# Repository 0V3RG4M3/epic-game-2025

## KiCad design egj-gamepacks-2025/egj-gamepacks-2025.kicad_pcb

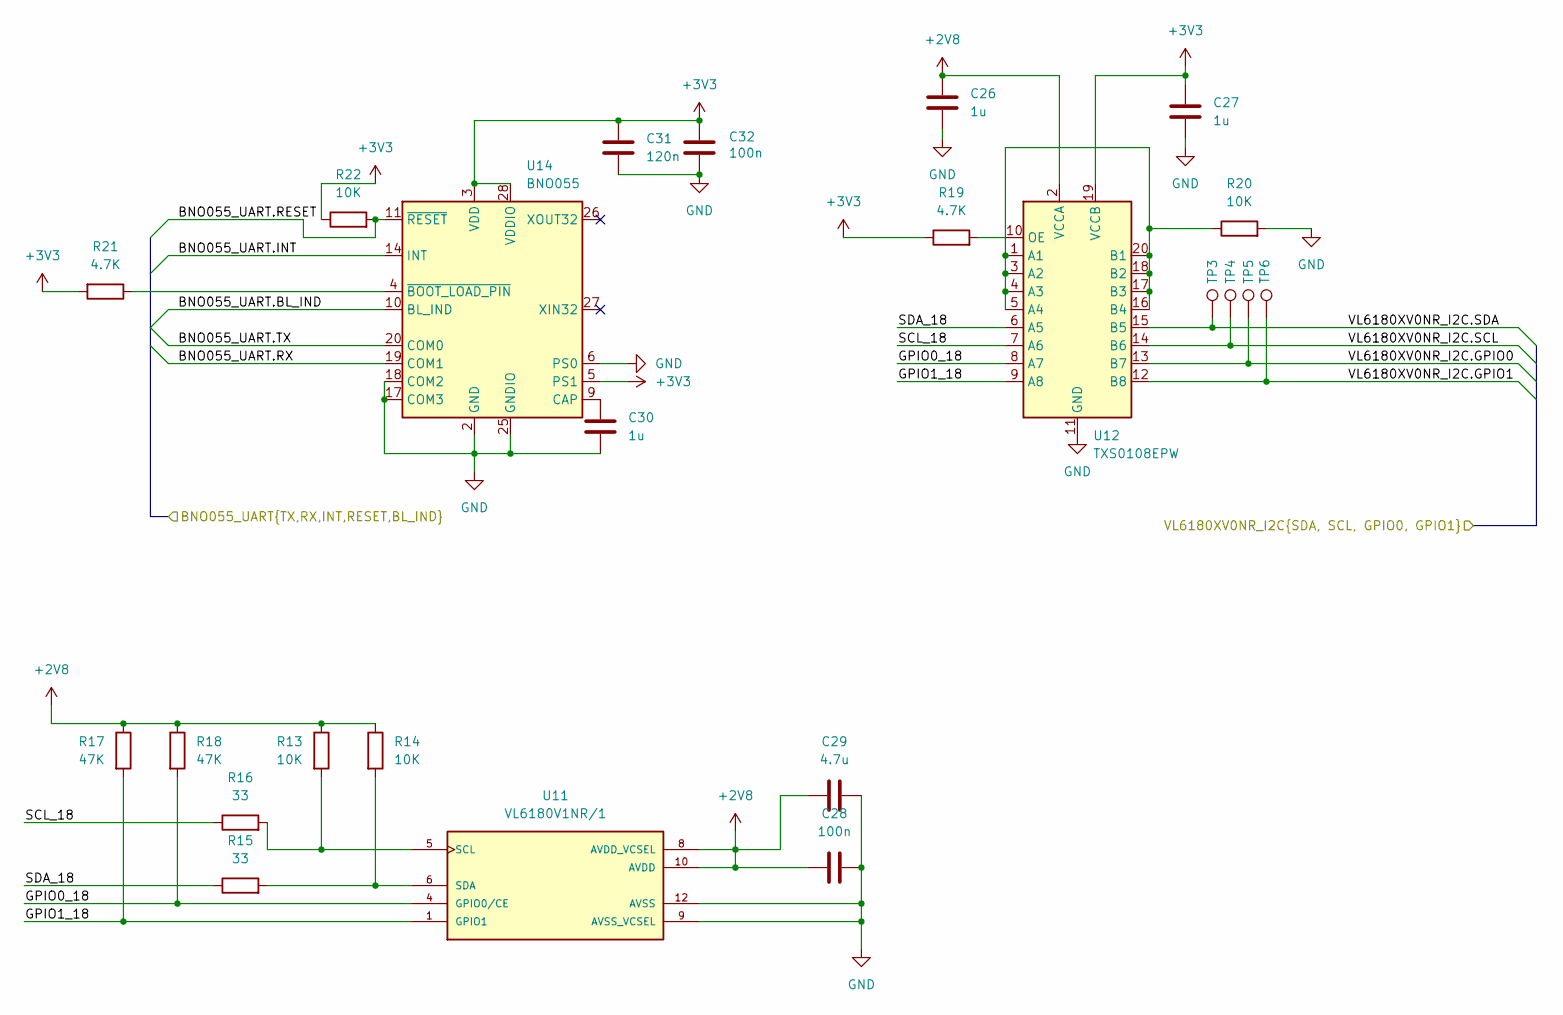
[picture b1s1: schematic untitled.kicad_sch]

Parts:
C26, C27, C30: 1u; C_0805_2012Metric; LCSC C28323
C28, C32: 100n; C_0805_2012Metric; LCSC C49678
C29: 4.7u; C_0805_2012Metric; LCSC C1779
C31: 120n; C_0805_2012Metric; LCSC C113854
R13, R14, R20, R22: 10K; R_0402_1005Metric; LCSC C25744
R15, R16: 33; R_0402_1005Metric; LCSC C25105
R17, R18: 47K; R_0402_1005Metric; LCSC C25792
R19, R21: 4.7K; R_0402_1005Metric; LCSC C25900
TP3, TP4, TP5, TP6: TestPoint; TestPoint_Keystone_5015_Micro_Mini; LCSC C2906768
U11: VL6180V1NR/1; LGA12R75P2X6_280X480X110; LCSC C2655167
U12: TXS0108EPW; TSSOP-20_4.4x6.5mm_P0.65mm; LCSC C17206
U14: BNO055; LGA-28_5.2x3.8mm_P0.5mm; LCSC C93216

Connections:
+2V8: C26.1, C28.1, C29.1, R13.1, R14.1, R17.1, R18.1, U11.8 (AVDD_VCSEL), U11.10 (AVDD), U12.2 (VCCA); also elsewhere on the board
+3V3: C27.1, C31.2, C32.2, R19.1, R21.2, R22.1, U12.19 (VCCB), U14.3 (VDD), U14.5 (PS1), U14.28 (VDDIO); also elsewhere on the board
/RP2350/BNO055_UART.BL_IND: U14.10 (BL_IND); also elsewhere on the board
/RP2350/BNO055_UART.INT: U14.14 (INT); also elsewhere on the board
/RP2350/BNO055_UART.RESET: R22.2, U14.11 (~RESET); also elsewhere on the board
/RP2350/BNO055_UART.RX: U14.19 (COM1); also elsewhere on the board
/RP2350/BNO055_UART.TX: U14.20 (COM0); also elsewhere on the board
/RP2350/VL6180XV0NR_I2C.GPIO0: TP5.1, U12.13 (B7); also elsewhere on the board
/RP2350/VL6180XV0NR_I2C.GPIO1: TP6.1, U12.12 (B8); also elsewhere on the board
/RP2350/VL6180XV0NR_I2C.SCL: TP4.1, U12.14 (B6); also elsewhere on the board
/RP2350/VL6180XV0NR_I2C.SDA: TP3.1, U12.15 (B5); also elsewhere on the board
/sensor_part/GPIO0_18: R18.2, U11.4 (GPIO0/CE), U12.8 (A7)
/sensor_part/GPIO1_18: R17.2, U11.1 (GPIO1), U12.9 (A8)
/sensor_part/SCL_18: R16.1, U12.7 (A6)
/sensor_part/SDA_18: R15.1, U12.6 (A5)
GND: C26.2, C27.2, C28.2, C29.2, C30.1, C31.1, C32.1, R20.2, U11.9 (AVSS_VCSEL), U11.12 (AVSS), U12.11 (GND), U14.2 (GND), U14.6 (PS0), U14.17 (COM3), U14.18 (COM2), U14.25 (GNDIO); also elsewhere on the board
unnamed: R13.2, R16.2, U11.5 (SCL)
unnamed: R14.2, R15.2, U11.6 (SDA)
unnamed: R20.1, U12.1 (A1), U12.3 (A2), U12.4 (A3), U12.5 (A4), U12.16 (B4), U12.17 (B3), U12.18 (B2), U12.20 (B1)
unnamed: R19.2, U12.10 (OE)
unnamed: C30.2, U14.9 (CAP)
unnamed: R21.1, U14.4 (~BOOT_LOAD_PIN)

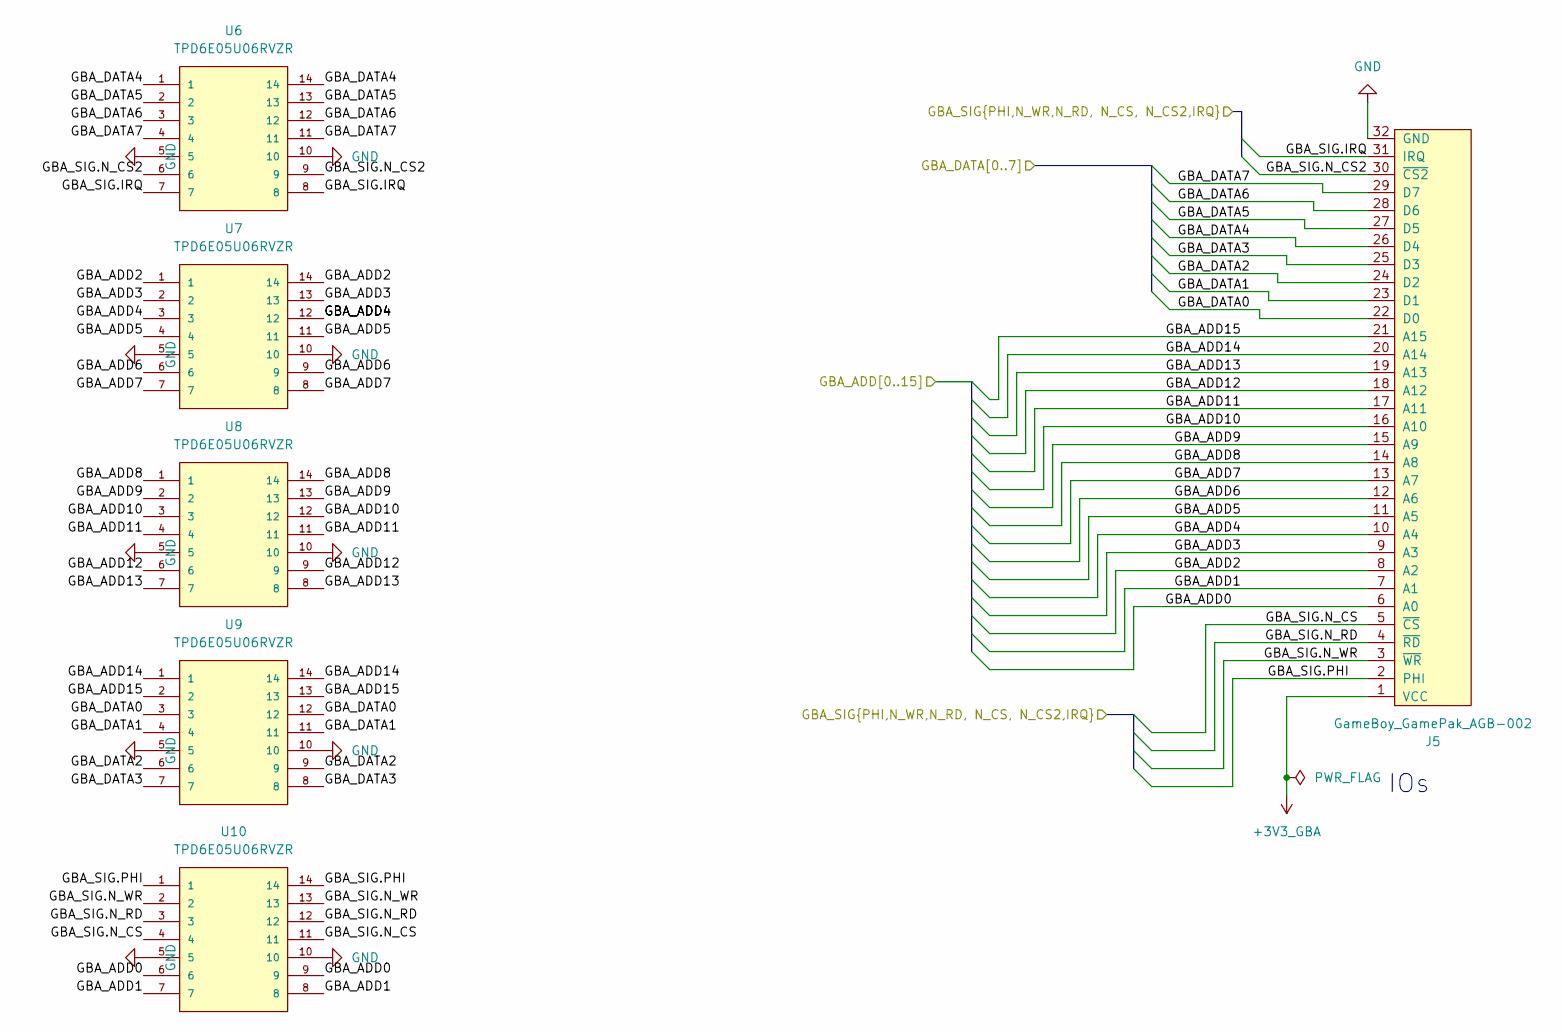
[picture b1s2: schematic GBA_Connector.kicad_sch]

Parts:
J5: GameBoy_GamePak_AGB-002; GameBoy_GamePak_AGB-002_P1.50mm_Edge
U6, U7, U8, U9, U10: TPD6E05U06RVZR; DFN-14_1.35x3.5mm_P0.5mm; PARTREV 02/23/17; LCSC C962978

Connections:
+3V3_GBA: J5.1 (VCC); also elsewhere on the board
/GBA_Connector/GBA_ADD0: J5.6 (A0), U10.6, U10.9; also elsewhere on the board
/GBA_Connector/GBA_ADD1: J5.7 (A1), U10.7, U10.8; also elsewhere on the board
/GBA_Connector/GBA_ADD2: J5.8 (A2), U7.1, U7.14; also elsewhere on the board
/GBA_Connector/GBA_ADD3: J5.9 (A3), U7.2, U7.13; also elsewhere on the board
/GBA_Connector/GBA_ADD4: J5.10 (A4), U7.3, U7.12; also elsewhere on the board
/GBA_Connector/GBA_ADD5: J5.11 (A5), U7.4, U7.11; also elsewhere on the board
/GBA_Connector/GBA_ADD6: J5.12 (A6), U7.6, U7.9; also elsewhere on the board
/GBA_Connector/GBA_ADD7: J5.13 (A7), U7.7, U7.8; also elsewhere on the board
/GBA_Connector/GBA_ADD8: J5.14 (A8), U8.1, U8.14; also elsewhere on the board
/GBA_Connector/GBA_ADD9: J5.15 (A9), U8.2, U8.13; also elsewhere on the board
/GBA_Connector/GBA_ADD10: J5.16 (A10), U8.3, U8.12; also elsewhere on the board
/GBA_Connector/GBA_ADD11: J5.17 (A11), U8.4, U8.11; also elsewhere on the board
/GBA_Connector/GBA_ADD12: J5.18 (A12), U8.6, U8.9; also elsewhere on the board
/GBA_Connector/GBA_ADD13: J5.19 (A13), U8.7, U8.8; also elsewhere on the board
/GBA_Connector/GBA_ADD14: J5.20 (A14), U9.1, U9.14; also elsewhere on the board
/GBA_Connector/GBA_ADD15: J5.21 (A15), U9.2, U9.13; also elsewhere on the board
/GBA_Connector/GBA_DATA0: J5.22 (D0), U9.3, U9.12; also elsewhere on the board
/GBA_Connector/GBA_DATA1: J5.23 (D1), U9.4, U9.11; also elsewhere on the board
/GBA_Connector/GBA_DATA2: J5.24 (D2), U9.6, U9.9; also elsewhere on the board
/GBA_Connector/GBA_DATA3: J5.25 (D3), U9.7, U9.8; also elsewhere on the board
/GBA_Connector/GBA_DATA4: J5.26 (D4), U6.1, U6.14; also elsewhere on the board
/GBA_Connector/GBA_DATA5: J5.27 (D5), U6.2, U6.13; also elsewhere on the board
/GBA_Connector/GBA_DATA6: J5.28 (D6), U6.3, U6.12; also elsewhere on the board
/GBA_Connector/GBA_DATA7: J5.29 (D7), U6.4, U6.11; also elsewhere on the board
/GBA_Connector/GBA_SIG.IRQ: J5.31 (IRQ), U6.7, U6.8; also elsewhere on the board
/GBA_Connector/GBA_SIG.N_CS: J5.5 (~CS), U10.4, U10.11; also elsewhere on the board
/GBA_Connector/GBA_SIG.N_CS2: J5.30 (~CS2), U6.6, U6.9; also elsewhere on the board
/GBA_Connector/GBA_SIG.N_RD: J5.4 (~RD), U10.3, U10.12; also elsewhere on the board
/GBA_Connector/GBA_SIG.N_WR: J5.3 (~WR), U10.2, U10.13; also elsewhere on the board
/GBA_Connector/GBA_SIG.PHI: J5.2 (PHI), U10.1, U10.14; also elsewhere on the board
GND: J5.32 (GND), U6.5, U6.10, U7.5, U7.10, U8.5, U8.10, U9.5, U9.10, U10.5, U10.10; also elsewhere on the board

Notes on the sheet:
IOs

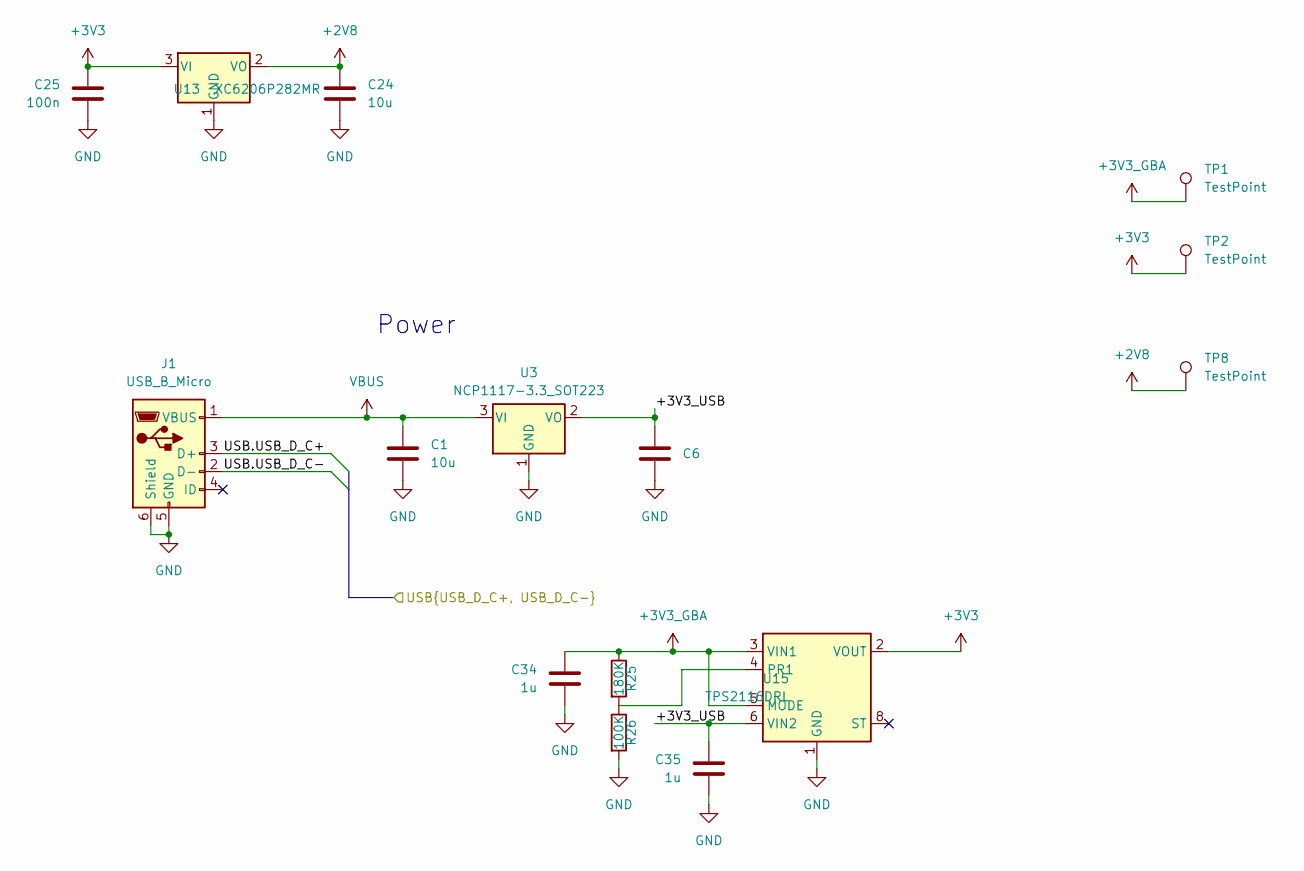
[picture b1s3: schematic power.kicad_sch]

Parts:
C1, C6, C24: 10u; C_0805_2012Metric; LCSC C15850
C25: 100n; C_0805_2012Metric; LCSC C49678
C34, C35: 1u; C_0402_1005Metric; LCSC C52923
J1: USB_B_Micro; USB_Micro-B_Amphenol_10103594-0001LF_Horizontal; LCSC C428495
R25: 180K; R_0402_1005Metric; LCSC C25760
R26: 100K; R_0402_1005Metric; LCSC C25741
TP1, TP2, TP8: TestPoint; TestPoint_Keystone_5015_Micro_Mini; LCSC C2906768
U3: NCP1117-3.3_SOT223; SOT-223-3_TabPin2; LCSC C26537
U13: XC6206P282MR; SOT-23-3; LCSC C347374
U15: TPS2116DRL; SOT-583-8; LCSC C3235557

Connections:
+2V8: C24.1, TP8.1, U13.2 (VO); also elsewhere on the board
+3V3: C25.1, TP2.1, U13.3 (VI), U15.2 (VOUT), U15.7 (VOUT); also elsewhere on the board
+3V3_GBA: C34.1, R25.1, TP1.1, U15.3 (VIN1), U15.5 (MODE); also elsewhere on the board
/Power/+3V3_USB: C6.1, C35.1, U3.2 (VO), U15.6 (VIN2)
/Power/USB.USB_D_C+: J1.3 (D+); also elsewhere on the board
/Power/USB.USB_D_C-: J1.2 (D-); also elsewhere on the board
GND: C1.2, C6.2, C24.2, C25.2, C34.2, C35.2, J1.5 (GND), J1.6 (Shield), R26.2, U3.1 (GND), U13.1 (GND), U15.1 (GND); also elsewhere on the board
unnamed: R25.2, R26.1, U15.4 (PR1)
VBUS: C1.1, J1.1 (VBUS), U3.3 (VI); also elsewhere on the board

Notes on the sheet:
Power

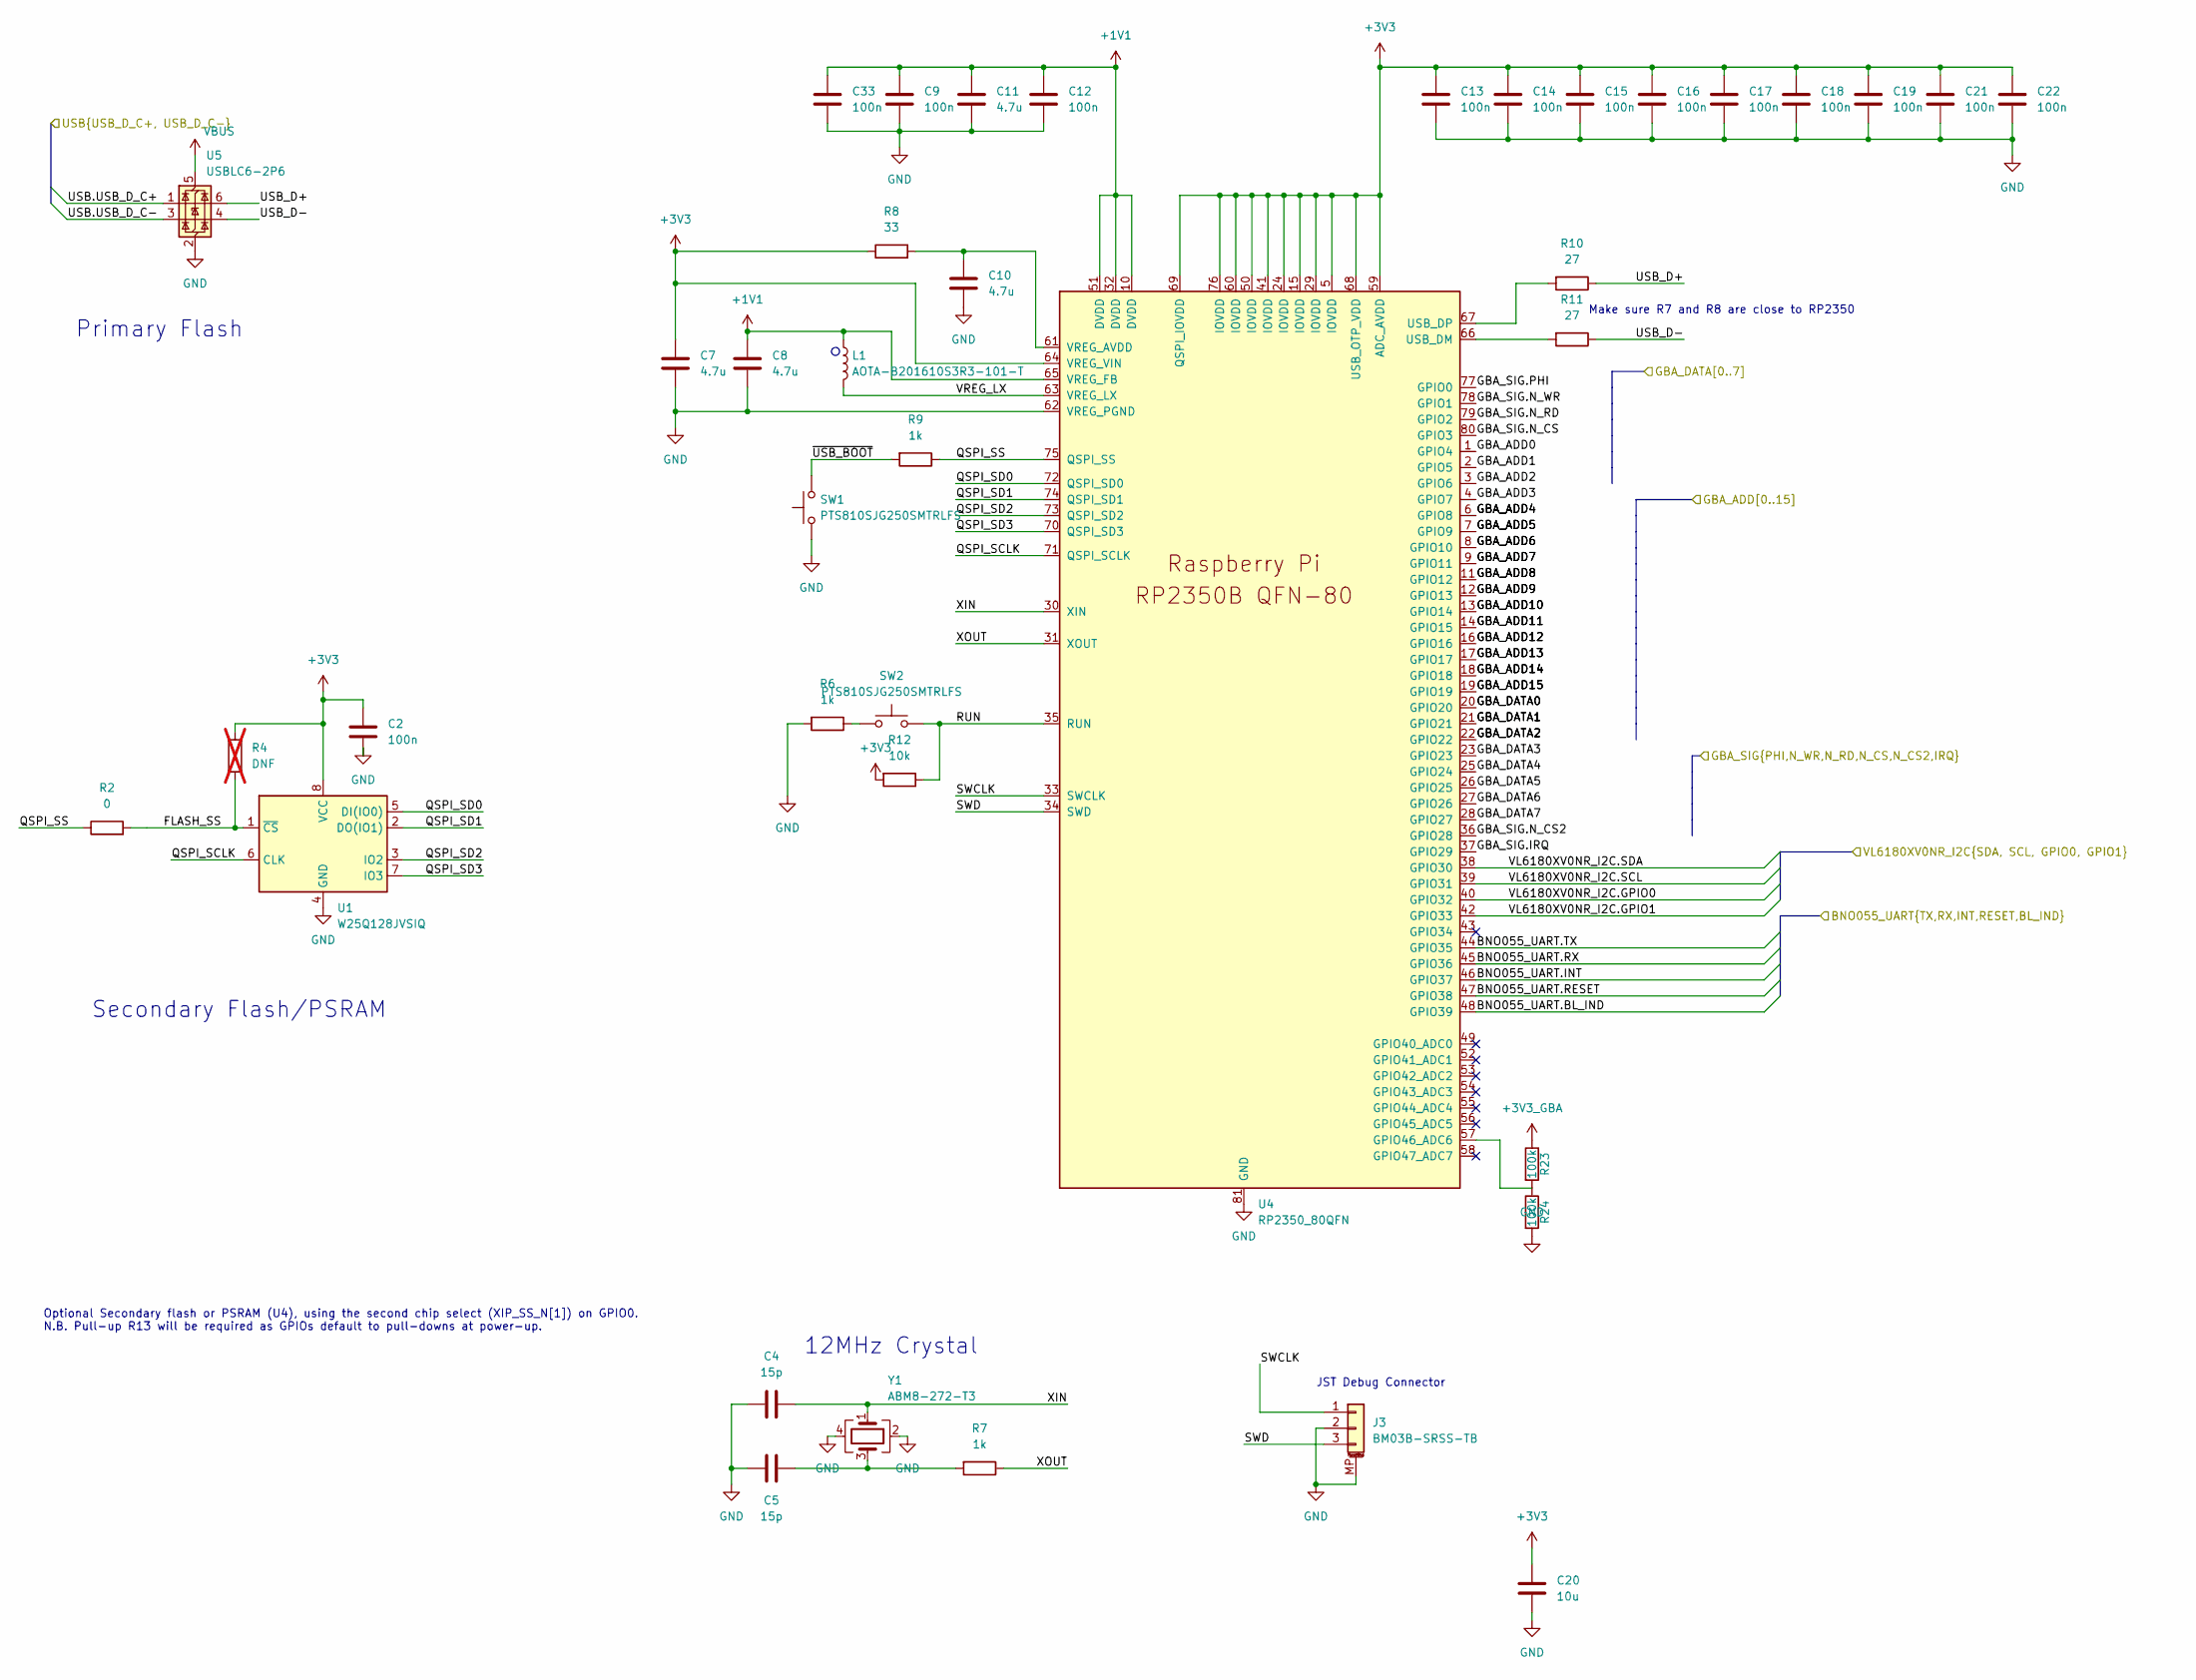
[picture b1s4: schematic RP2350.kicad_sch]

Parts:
C2, C9, C12, C13, C14, C15, C16, C17, C18, C19, C21, C22, C33: 100n; C_0402_1005Metric; LCSC C1525
C4, C5: 15p; C_0402_1005Metric; LCSC C1548
C7, C8: 4.7u; C_0402_1005Metric_small_pads; LCSC C23733
C10, C11: 4.7u; C_0402_1005Metric; LCSC C23733
C20: 10u; C_0805_2012Metric; LCSC C15850
J3: BM03B-SRSS-TB; JST_SH_BM03B-SRSS-TB_1x03-1MP_P1.00mm_Vertical; LCSC C160389
L1: AOTA-B201610S3R3-101-T; L_pol_2016; LCSC C42411119
R2: 0; R_0402_1005Metric; LCSC C17168
R4: DNF; R_0402_1005Metric; not fitted
R6, R7, R9: 1k; R_0402_1005Metric; LCSC C11702
R8: 33; R_0402_1005Metric; LCSC C25105
R10, R11: 27; R_0402_1005Metric; LCSC C25100
R12: 10k; R_0402_1005Metric; LCSC C25744
R23, R24: 100k; R_0402_1005Metric; LCSC C25741
SW1, SW2: PTS810SJG250SMTRLFS; SW_SPST_PTS810; LCSC C221895
U1: W25Q128JVSIQ; SOIC-8_5.3x5.3mm_P1.27mm; LCSC C97521
U4: RP2350_80QFN; RP2350-QFN-80-1EP_10x10_P0.4mm_EP3.4x3.4mm_ThermalVias; LCSC C42415655
U5: USBLC6-2P6; SOT-666; LCSC C15999
Y1: ABM8-272-T3; Crystal_SMD_3225-4Pin_3.2x2.5mm; LCSC C20625731

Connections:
+1V1: C8.1, C9.1, C11.1, C12.1, C33.1, L1.1, U4.10 (DVDD), U4.32 (DVDD), U4.51 (DVDD), U4.65 (VREG_FB)
+3V3: C2.1, C7.1, C13.1, C14.1, C15.1, C16.1, C17.1, C18.1, C19.1, C20.1, C21.1, C22.1, R4.1, R8.1, R12.2, U1.8 (VCC), U4.5 (IOVDD), U4.15 (IOVDD), U4.24 (IOVDD), U4.29 (IOVDD), U4.41 (IOVDD), U4.50 (IOVDD), U4.59 (ADC_AVDD), U4.60 (IOVDD), U4.64 (VREG_VIN), U4.68 (USB_OTP_VDD), U4.69 (QSPI_IOVDD), U4.76 (IOVDD); also elsewhere on the board
+3V3_GBA: R23.1; also elsewhere on the board
/GBA_Connector/GBA_ADD0: U4.1 (GPIO4); also elsewhere on the board
/GBA_Connector/GBA_ADD1: U4.2 (GPIO5); also elsewhere on the board
/GBA_Connector/GBA_ADD2: U4.3 (GPIO6); also elsewhere on the board
/GBA_Connector/GBA_ADD3: U4.4 (GPIO7); also elsewhere on the board
/GBA_Connector/GBA_ADD4: U4.6 (GPIO8); also elsewhere on the board
/GBA_Connector/GBA_ADD5: U4.7 (GPIO9); also elsewhere on the board
/GBA_Connector/GBA_ADD6: U4.8 (GPIO10); also elsewhere on the board
/GBA_Connector/GBA_ADD7: U4.9 (GPIO11); also elsewhere on the board
/GBA_Connector/GBA_ADD8: U4.11 (GPIO12); also elsewhere on the board
/GBA_Connector/GBA_ADD9: U4.12 (GPIO13); also elsewhere on the board
/GBA_Connector/GBA_ADD10: U4.13 (GPIO14); also elsewhere on the board
/GBA_Connector/GBA_ADD11: U4.14 (GPIO15); also elsewhere on the board
/GBA_Connector/GBA_ADD12: U4.16 (GPIO16); also elsewhere on the board
/GBA_Connector/GBA_ADD13: U4.17 (GPIO17); also elsewhere on the board
/GBA_Connector/GBA_ADD14: U4.18 (GPIO18); also elsewhere on the board
/GBA_Connector/GBA_ADD15: U4.19 (GPIO19); also elsewhere on the board
/GBA_Connector/GBA_DATA0: U4.20 (GPIO20); also elsewhere on the board
/GBA_Connector/GBA_DATA1: U4.21 (GPIO21); also elsewhere on the board
/GBA_Connector/GBA_DATA2: U4.22 (GPIO22); also elsewhere on the board
/GBA_Connector/GBA_DATA3: U4.23 (GPIO23); also elsewhere on the board
/GBA_Connector/GBA_DATA4: U4.25 (GPIO24); also elsewhere on the board
/GBA_Connector/GBA_DATA5: U4.26 (GPIO25); also elsewhere on the board
/GBA_Connector/GBA_DATA6: U4.27 (GPIO26); also elsewhere on the board
/GBA_Connector/GBA_DATA7: U4.28 (GPIO27); also elsewhere on the board
/GBA_Connector/GBA_SIG.IRQ: U4.37 (GPIO29); also elsewhere on the board
/GBA_Connector/GBA_SIG.N_CS: U4.80 (GPIO3); also elsewhere on the board
/GBA_Connector/GBA_SIG.N_CS2: U4.36 (GPIO28); also elsewhere on the board
/GBA_Connector/GBA_SIG.N_RD: U4.79 (GPIO2); also elsewhere on the board
/GBA_Connector/GBA_SIG.N_WR: U4.78 (GPIO1); also elsewhere on the board
/GBA_Connector/GBA_SIG.PHI: U4.77 (GPIO0); also elsewhere on the board
/Power/USB.USB_D_C+: U5.1 (I/O1); also elsewhere on the board
/Power/USB.USB_D_C-: U5.3 (I/O2); also elsewhere on the board
/RP2350/BNO055_UART.BL_IND: U4.48 (GPIO39); also elsewhere on the board
/RP2350/BNO055_UART.INT: U4.46 (GPIO37); also elsewhere on the board
/RP2350/BNO055_UART.RESET: U4.47 (GPIO38); also elsewhere on the board
/RP2350/BNO055_UART.RX: U4.45 (GPIO36); also elsewhere on the board
/RP2350/BNO055_UART.TX: U4.44 (GPIO35); also elsewhere on the board
/RP2350/FLASH_SS: R2.2, R4.2, U1.1 (~CS)
/RP2350/QSPI_SCLK: U1.6 (CLK), U4.71 (QSPI_SCLK)
/RP2350/QSPI_SD0: U1.5 (DI(IO0)), U4.72 (QSPI_SD0)
/RP2350/QSPI_SD1: U1.2 (DO(IO1)), U4.74 (QSPI_SD1)
/RP2350/QSPI_SD2: U1.3 (IO2), U4.73 (QSPI_SD2)
/RP2350/QSPI_SD3: U1.7 (IO3), U4.70 (QSPI_SD3)
/RP2350/QSPI_SS: R2.1, R9.1, U4.75 (QSPI_SS)
/RP2350/RUN: R12.1, SW2.2, U4.35 (RUN)
/RP2350/SWCLK: J3.1, U4.33 (SWCLK)
/RP2350/SWD: J3.3, U4.34 (SWD)
/RP2350/USB_D+: R10.1, U5.6 (I/O1)
/RP2350/USB_D-: R11.1, U5.4 (I/O2)
/RP2350/VL6180XV0NR_I2C.GPIO0: U4.40 (GPIO32); also elsewhere on the board
/RP2350/VL6180XV0NR_I2C.GPIO1: U4.42 (GPIO33); also elsewhere on the board
/RP2350/VL6180XV0NR_I2C.SCL: U4.39 (GPIO31); also elsewhere on the board
/RP2350/VL6180XV0NR_I2C.SDA: U4.38 (GPIO30); also elsewhere on the board
/RP2350/VREG_LX: L1.2, U4.63 (VREG_LX)
/RP2350/XIN: C4.1, U4.30 (XIN), Y1.1
/RP2350/XOUT: R7.1, U4.31 (XOUT)
/RP2350/~USB_BOOT: R9.2, SW1.2
GND: C2.2, C4.2, C5.2, C7.2, C8.2, C9.2, C10.2, C11.2, C12.2, C13.2, C14.2, C15.2, C16.2, C17.2, C18.2, C19.2, C20.2, C21.2, C22.2, C33.2, J3.2, J3.MP (MountPin), R6.2, R24.2, SW1.1, U1.4 (GND), U4.62 (VREG_PGND), U4.81 (GND), U5.2 (GND), Y1.2, Y1.4; also elsewhere on the board
unnamed: C5.1, R7.2, Y1.3
unnamed: R6.1, SW2.1
unnamed: R23.2, R24.1, U4.57 (GPIO46_ADC6)
unnamed: R11.2, U4.66 (USB_DM)
unnamed: R10.2, U4.67 (USB_DP)
unnamed: C10.1, R8.2, U4.61 (VREG_AVDD)
VBUS: U5.5 (VBUS); also elsewhere on the board

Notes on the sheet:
Make sure R7 and R8 are close to RP2350
Primary Flash
JST Debug Connector
12MHz Crystal
Secondary Flash/PSRAM
Optional Secondary flash or PSRAM (U4), using the second chip select (XIP_SS_N[1]) on GPIO0. N.B. Pull-up R13 will be required as GPIOs default to pull-downs at power-up.

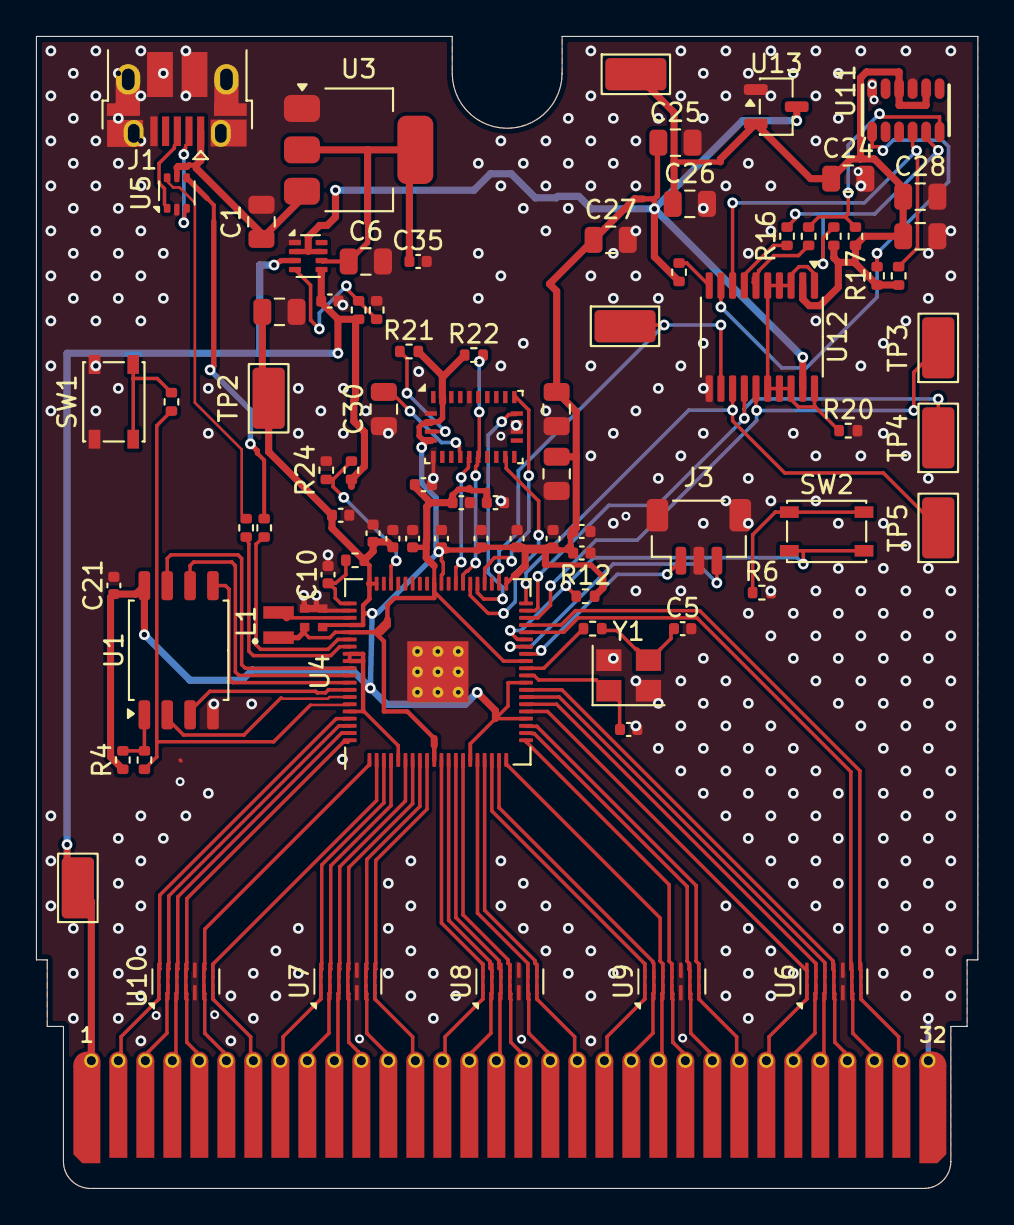
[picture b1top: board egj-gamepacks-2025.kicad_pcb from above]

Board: 2 copper layers, 52.3 x 64.0 mm, 84 parts (0 on the bottom side), 81 nets.

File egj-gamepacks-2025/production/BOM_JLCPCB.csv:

Comment,Designator,Footprint,LCSC Part #
10u,"C1,C6,C20,C24",C_0805_2012Metric,C15850
100n,"C2,C9,C12,C13,C14,C15,C16,C17,C18,C19,C21,C22,C33",C_0402_1005Metric,C1525
15p,"C4,C5",C_0402_1005Metric,C1548
4.7u,"C7,C8",C_0402_1005Metric_small_pads,C23733
4.7u,"C10,C11",C_0402_1005Metric,C23733
100n,"C25,C28,C32",C_0805_2012Metric,C49678
1u,"C26,C27,C30",C_0805_2012Metric,C28323
4.7u,C29,C_0805_2012Metric,C1779
120n,C31,C_0805_2012Metric,C113854
1u,"C34,C35",C_0402_1005Metric,C52923
USB_B_Micro,J1,USB_Micro-B_Amphenol_10103594-0001LF_Horizontal,C428495
BM03B-SRSS-TB,J3,JST_SH_BM03B-SRSS-TB_1x03-1MP_P1.00mm_Vertical,C160389
AOTA-B201610S3R3-101-T,L1,L_pol_2016,C42411119
0,R2,R_0402_1005Metric,C17168
1k,"R6,R7,R9",R_0402_1005Metric,C11702
33,"R8,R15,R16",R_0402_1005Metric,C25105
27,"R10,R11",R_0402_1005Metric,C25100
10k,R12,R_0402_1005Metric,C25744
10K,"R13,R14,R20,R22",R_0402_1005Metric,C25744
47K,"R17,R18",R_0402_1005Metric,C25792
4.7K,"R19,R21",R_0402_1005Metric,C25900
100k,"R23,R24",R_0402_1005Metric,C25741
180K,R25,R_0402_1005Metric,C25760
100K,R26,R_0402_1005Metric,C25741
PTS810SJG250SMTRLFS,"SW1,SW2",SW_SPST_PTS810,C221895
W25Q128JVSIQ,U1,SOIC-8_5.3x5.3mm_P1.27mm,C97521
NCP1117-3.3_SOT223,U3,SOT-223-3_TabPin2,C26537
RP2350_80QFN,U4,RP2350-QFN-80-1EP_10x10_P0.4mm_EP3.4x3.4mm_ThermalVias,C42415655
USBLC6-2P6,U5,SOT-666,C15999
TPD6E05U06RVZR,"U6,U7,U8,U9,U10",DFN-14_1.35x3.5mm_P0.5mm,C962978
VL6180V1NR/1,U11,LGA12R75P2X6_280X480X110,C2655167
TXS0108EPW,U12,TSSOP-20_4.4x6.5mm_P0.65mm,C17206
XC6206P282MR,U13,SOT-23-3,C347374
BNO055,U14,LGA-28_5.2x3.8mm_P0.5mm,C93216
TPS2116DRL,U15,SOT-583-8,C3235557
ABM8-272-T3,Y1,Crystal_SMD_3225-4Pin_3.2x2.5mm,C20625731

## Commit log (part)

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2025-04-03 PCB Design
2025-04-10 ADD: new design
2025-04-10 ADD: schema
2025-04-21 add new schemas
2025-05-20 ADD: add datasheet and update schema
